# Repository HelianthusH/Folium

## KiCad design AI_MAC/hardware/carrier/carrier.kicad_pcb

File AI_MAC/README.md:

# VoiceCard 独立录音与 Windows 语音输入器

Folium 项目许可：原创软件采用 [MIT](LICENSE.md)，原创硬件设计采用 CERN-OHL-S v2，原创文档采用 CC BY 4.0。固件、Windows 便携助手与离线模型的第三方许可和来源见 [随包声明](THIRD_PARTY_NOTICES.md)。发布包中附有对应的许可全文。

先看 [逐针接线、BOM 与外壳装配](hardware/ASSEMBLY.md)。第一次试机只需 Sense 主板、3.3 V 卡座、FAT32 卡、两个常开按键和 USB 电源。完整电池版的物料预算为 **¥211**。工作区含可刷固件、Windows 便携助手和制板文件。实机测试请用 [验收记录表](docs/ACCEPTANCE.md)。

## 一、总体设计

|模块|输入、职责与输出|
|---|---|
|XIAO Sense 与固件|板载 PDM 麦克风以标称 16 kHz、单声道、16 位采集。驱动提供缓冲，应用按块编码。录音键切换启停，绿色表示采集、红色表示故障。|
|microSD 与 RTC|独立写 WAV、逐段清单及带 CRC 的双份状态记录。离线时间来源为 PCF8563，录音长度来源为采样计数。|
|USB / BLE|录音期间按住听写键，固件将同一批新录音块传给已订阅的助手。单独使用听写键时也会保存短会话。|
|Windows 11 助手|本地中英流式识别、字幕、草稿记录和输入目标绑定。WorkBuddy、Codex 使用前台窗口与输入控件，Claude Code 使用助手启动的专用控制台。用户可混合键入、听写和修改，最后自行发送。|
|供电|USB-C 或 Qi 接收片供 BQ24074，电池接 BAT，电源路径输出经 5 V 升压供主板。两种充电入口共用一个面板插座。|

状态依次为 IDLE、STARTING、RECORDING、STOPPING、STOPPED。启动检查卡和容量并初始化麦克风，停止时排空可读缓冲、定稿当前 WAV、写清单。遇错进入 ERROR。正常断电前停录并等绿灯熄灭。意外断电后依双副本日志验证末段、修正文件长度，再依据录音意图续录。断电期间没有采样，以 gap_after 登记未知间隔。

## 二、接口契约

详情与调用示例见 [接口协议](docs/PROTOCOL.md)。电脑脚本通过当前用户的 Windows 命名管道调用助手，助手再通过 USB CDC 或已加密的 BLE GATT 链路访问设备。首次绑定用 USB 和实体双键确认。无需智能体 API 密钥。

## 三、实现产物

|入口|用途|
|---|---|
|[voicecard.uf2](release/voicecard.uf2) · [固件源码](firmware/src/main.c)|Zephyr 4.2.0，板型 xiao_ble/nrf52840/sense|
|[Windows 助手](release/VoiceCard/VoiceCard.exe) · [桌面源码](desktop/app.py)|解压后保留同目录的 _internal、models 和 config。双击运行，关闭主窗口后可从托盘再次打开。|
|[配置](config/voicecard.json) · [启动脚本](scripts/run.ps1)|首次启动复制到 %LOCALAPPDATA%\VoiceCard\voicecard.json。改 USB 端口、连接方式或可执行文件白名单后，从托盘退出并重启。|
|[载板 PCB](hardware/carrier/carrier.kicad_pcb) · [Gerber＋钻孔](hardware/carrier/carrier-gerber.zip)|2×7 插座转接板，外围模块按装配表接线|
|[模块级接线原理图](hardware/schematic/assembly.sch)|KiCad 可编辑原理图，打开时保留同目录符号库。面板 VBUS_IN 与本地 V5_LOCAL 分网。|
|[底壳](hardware/enclosure/base.stl) · [盖板](hardware/enclosure/lid.stl) · [可编辑外壳](hardware/enclosure/case.scad)|按所购模块微调开孔、固定位置与高度|
|[归档逻辑](desktop/archive.py) · [测试](tests/test_voicecard.py)|按卡或 USB 查询、恢复导出、SHA-256 核验|

### 保存、空间与导出

默认 IMA ADPCM WAV，每块 256 B 存 505 个采样点，静音照常记录。码流约 29.2 MB/小时，48 小时约 1.40 GB。PCM16 逐采样保存，48 小时约 5.53 GB。以上是十进制容量，另有头部、清单和 FAT 开销。录音约每 5 分钟在完整块边界切段，录音时只保留有限的缓冲。16 GB 卡留足两天容量。

会话目录为 REC/YYYY/MM/DD/十六位会话号/，日期取会话开始 UTC，跨午夜仍属于同一会话。RTC 失效时使用 REC/UNSYNCED/。0001.wav 对应 0001.json，字段含设备号、固件版本、会话号、段号、UTC、时钟可信度、编码、采样位置、样本数、字节数、SHA-256、结束原因及缺口。设备按目录与清单检索，助手重建 SQLite 时间索引。

每次开新段检查空间。低于 512 MiB 时依段末 UTC 从最老的段清理，只清理已封存且超过 48 小时的段，未校时的段保留。空间仍不足时进入 NO_SPACE。导出先写 .partial 目录，再核对长度和整段 SHA-256；通过后发布 export-… 目录及 SHA256.json。导出中断后用相同参数重试，校验失败的副本保留 .corrupt 扩展名。卡上最近 48 小时的保护依赖可信 RTC，校时前先确认电脑时间。

## 四、实施计划与首次使用

1. **独立试录。** 按装配表焊接 SPI 卡座、按键，插入单分区 FAT32 卡。用数据线接 XIAO，快速双击 RESET 进入 UF2 引导盘，把 release/voicecard.uf2 复制到引导盘，等主板重启。接独立 USB 电源，按录音键开始，过 10 秒再按一次。确认绿灯熄灭后断电、取卡播放 WAV。首次无 RTC 时间时到 UNSYNCED 目录查找。若无引导盘，先核对数据线、Sense 型号及原厂 UF2 引导程序。
2. **接便携供电。** 先限流测电源路径，再接电池和 Qi，测单独录音及录音加 BLE 两档电池端平均电流。预算为 44 小时独立录音加 4 小时听写，总耗电上限 2400 mAh。记录电芯与模块温升后再合壳。
3. **启用听写。** Windows 解压完整目录，运行 release/VoiceCard/VoiceCard.exe。插 USB，必要时指定 COM 口。同时按两键后松开，30 秒内点“USB 绑定”。回到助手查状态并确认时钟。点“绑定 workbuddy”或“绑定 codex”后在 4 秒内点击相应软件的草稿输入框。Claude Code 先运行 scripts/claude.ps1，再选择 claude_code 并切到专用控制台。按住听写键说话，松开后检查草稿。若输入框不支持辅助功能，用“打开草稿记录”复制定稿。
4. **无线使用和归档。** USB 绑定成功后有 120 秒首次蓝牙配对窗口。此期间在 Windows 蓝牙设置中配对 VoiceCard，然后把用户配置 transport 改为 ble 并重启助手。已配对电脑以后可直接重连。超时请重新双键确认并执行 USB 绑定，必要时先在 Windows 移除旧的配对。多台设备时指定 ble_address。批量导出切回 USB，或停录、断电后用读卡器。定版前完成 48 小时整机测试和三款应用的 USB、BLE 六组测试。

在项目根目录的 PowerShell 执行。脚本中的 E: 替换为卡的盘符。

```powershell
.\scripts\status.ps1
.\scripts\start.ps1 -Codec ima
.\scripts\stop.ps1
.\scripts\list.ps1 --card E:\
.\scripts\export.ps1 -Card E:\ -Dest D:\VoiceExports
.\scripts\verify.ps1 -Dest D:\VoiceExports\export-具体批次号
```

源码模式需要 Python 3.10 x64。运行 scripts/install.ps1 安装锁定版本的依赖及模型，然后执行 scripts/run.ps1。固件构建需要 ARM 嵌入式工具链、Git、CMake、Ninja、west 和 Zephyr 指定模块。Windows 下构建源和 Zephyr 工作树使用纯英文物理路径以兼容工具链。模型首次下载时校验上游归档的 SHA-256，便携版已带模型。

## 五、验证验收

主机测试已覆盖读卡检索、坏段检测、断点续传、草稿去重、命名管道和离线模型。续航、USB/Qi 充电、麦克风声音、掉电损失、蓝牙吞吐以及三款智能体版本兼容性须在装配后填写。[验收步骤与已知边界](docs/ACCEPTANCE.md)

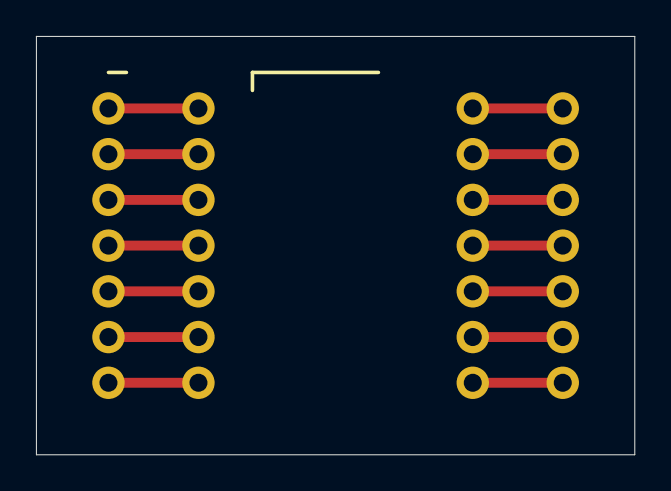
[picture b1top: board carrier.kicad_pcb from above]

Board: 2 copper layers, 33.2 x 23.2 mm, 28 parts (0 on the bottom side), 14 nets.

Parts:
J1: REC; ThroughHole
J2: PTT; ThroughHole
J3: D2; ThroughHole
J4: SD_CS; ThroughHole
J5: SDA; ThroughHole
J6: SCL; ThroughHole
J7: D6; ThroughHole
J8: V5_LOCAL; ThroughHole
J9: GND; ThroughHole
J10: 3V3; ThroughHole
J11: MOSI; ThroughHole
J12: MISO; ThroughHole
J13: SCK; ThroughHole
J14: D7; ThroughHole
W1: REC; ThroughHole
W2: PTT; ThroughHole
W3: D2; ThroughHole
W4: SD_CS; ThroughHole
W5: SDA; ThroughHole
W6: SCL; ThroughHole
W7: D6; ThroughHole
W8: V5_LOCAL; ThroughHole
W9: GND; ThroughHole
W10: 3V3; ThroughHole
W11: MOSI; ThroughHole
W12: MISO; ThroughHole
W13: SCK; ThroughHole
W14: D7; ThroughHole

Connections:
3V3: J10.1, W10.1
D2: J3.1, W3.1
D6: J7.1, W7.1
D7: J14.1, W14.1
GND: J9.1, W9.1
MISO: J12.1, W12.1
MOSI: J11.1, W11.1
PTT: J2.1, W2.1
REC: J1.1, W1.1
SCK: J13.1, W13.1
SCL: J6.1, W6.1
SDA: J5.1, W5.1
SD_CS: J4.1, W4.1
V5_LOCAL: J8.1, W8.1
